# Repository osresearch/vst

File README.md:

v.st vector board
====

This is the firmware and example code for the opensource harwdare
quad-DAC vector board.  It can be used with MAME to display the
vectors from 1970s and 80s games like Starwars or Asteroids
on vectorscopes and XY monitors like the Vectrex, as well as
with new art projects.

More details at https://trmm.net/V.st and https://trmm.net/MAME

## Building the Board
A full Bill of Materials can be found [here](BOM.md).

## Flashing the Firmware
To flash the firmware, make sure you have [Teensyduino](https://www.pjrc.com/teensy/td_download.html) installed.

Clone this repository and load *teensyv/teensyv.ino* in the Arduino IDE. Next select *Teensy 3.1 / 3.2* from the *Tools -> Board* menu in the Arduino IDE. Hit verify and follow the on screen instructions to flash your Teensy with the firmware.

## Running the Demos
Make sure you have [Processing](https://processing.org/) installed and your Teensy is flashed with the firmware.

Open *processingDemo/processingDemo.pde* in Processing. As soon as you hit run and your v.st board is attached to the computer, the demo starts playing on your screen and should be visible on the device attached to your v.st.

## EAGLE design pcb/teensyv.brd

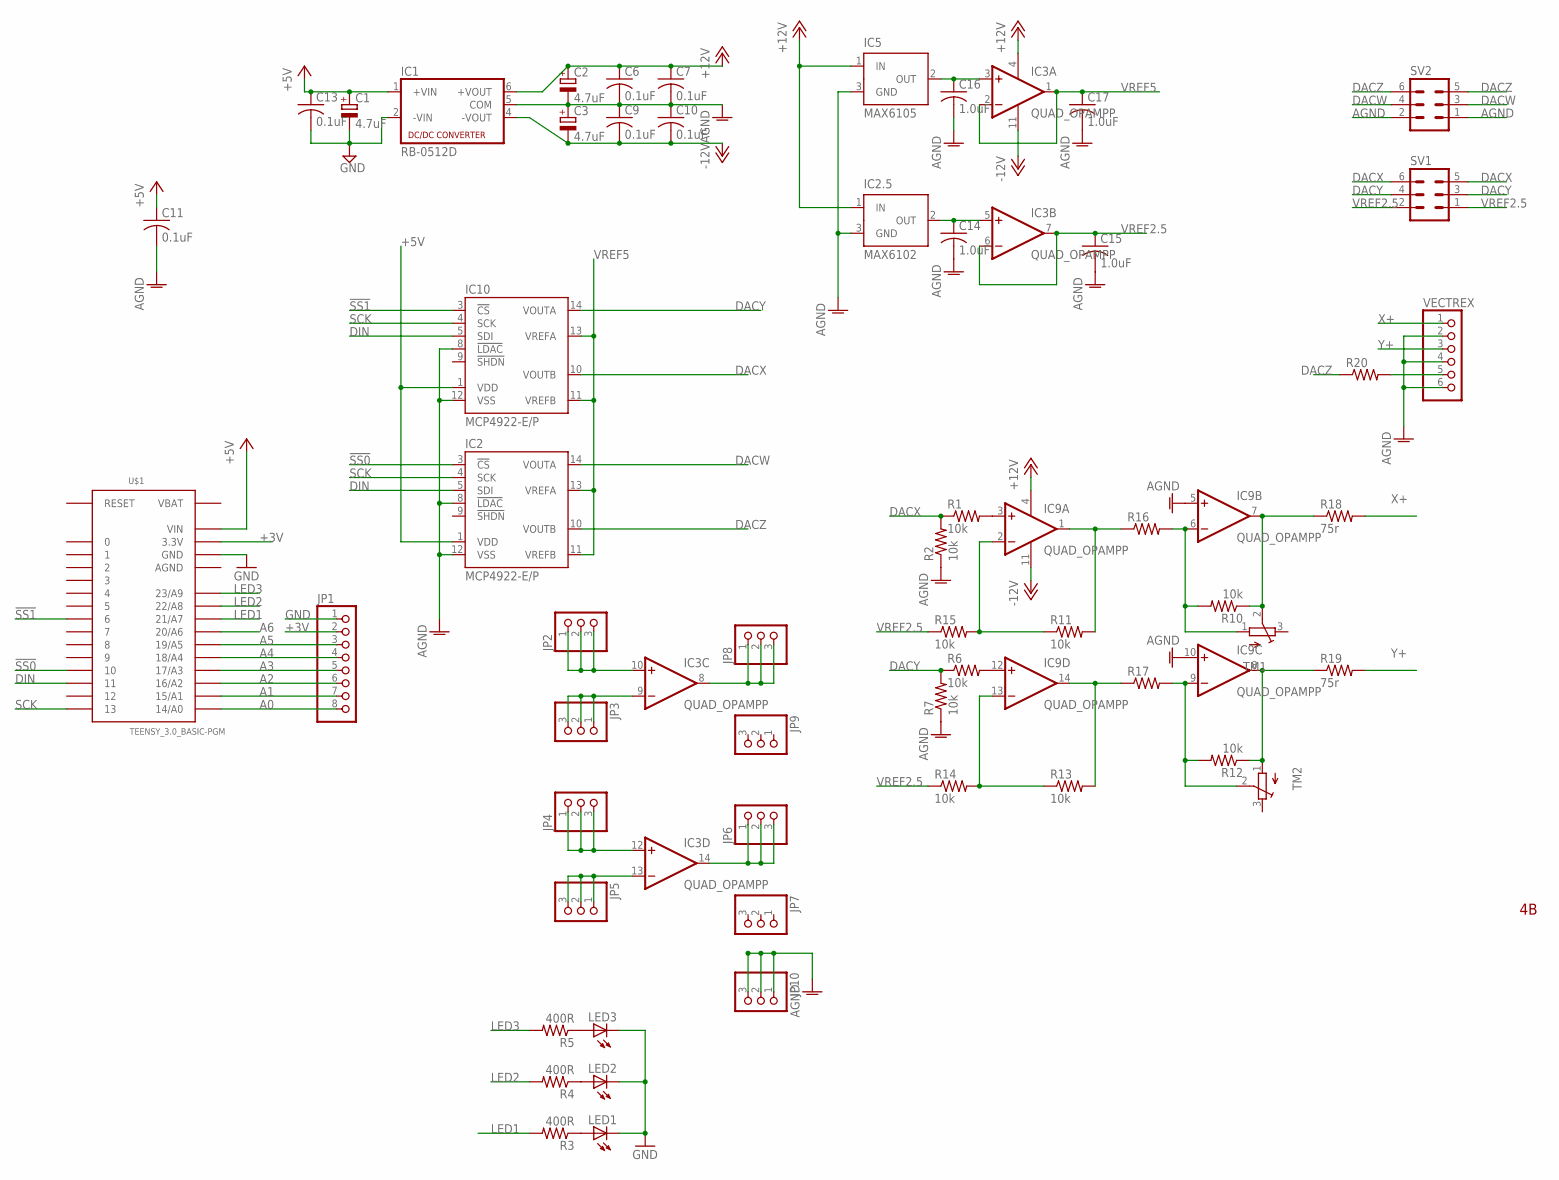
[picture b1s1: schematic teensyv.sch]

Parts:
C1, C2, C3: 4.7uF; E1,8-4
C6, C7, C9, C10, C11, C13: 0.1uF; C025-024X044
C14, C15, C16, C17: 1.0uF; C025-024X044
IC1: RB-0512D; NMA
IC2, IC10: MCP4922-E/P; DIL14
IC2.5: MAX6102; SOT23
IC3, IC9: QUAD_OPAMPP; DIL14
IC5: MAX6105; SOT23
JP1: PINHD-1X8CLEANBIG; 1X08-CLEANBIG
JP2, JP3, JP4, JP5, JP6, JP7, JP8, JP9, JP10: PINHD-1X3; 1X03
LED1, LED2, LED3: LED5MM
R1, R2, R6, R7, R10, R11, R12, R13, R14, R15: 10k; 0204V
R3, R4, R5: 400R; 0204V
R16, R17, R20: R-US_0204/7; 0204/7
R18, R19: 75r; 0204V
SV1, SV2: MA03-2
TM1, TM2: TRIMPOTTC33X; TC33X
U$1: TEENSY_3.0_BASIC-PGM
VECTREX: PINHD-1X6; 1X06

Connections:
!SS0: IC2.3 (!CS), U$1.10
!SS1: IC10.3 (!CS), U$1.6
+3V: JP1.2, U$1.3.3V, U$1.3.3V1 (3.3V)
+5V: C1.+, C11.1, C13.1, IC1.1 (+VIN), IC2.1 (VDD), IC10.1 (VDD), U$1.VIN
+12V: C2.+, C6.1, C7.1, IC1.6 (+VOUT), IC2.5.1 (IN), IC3.4 (V+), IC5.1 (IN), IC9.4 (V+)
-12V: C3.-, C9.2, C10.2, IC1.4 (-VOUT), IC3.11 (V-), IC9.11 (V-)
A0: JP1.8, U$1.14/A0
A1: JP1.7, U$1.15/A1
A2: JP1.6, U$1.16/A2
A3: JP1.5, U$1.17/A3
A4: JP1.4, U$1.18/A4
A5: JP1.3, U$1.19/A5
A6: U$1.20/A6
AGND: C2.-, C3.+, C6.2, C7.2, C9.1, C10.1, C11.2, C14.2, C15.2, C16.2, C17.2, IC1.5 (COM), IC2.8 (!LDAC), IC2.12 (VSS), IC2.5.3 (GND), IC5.3 (GND), IC9.5 (+IN), IC9.10 (+IN), IC10.8 (!LDAC), IC10.12 (VSS), JP10.1, JP10.2, JP10.3, R2.1, R7.1, SV2.1, SV2.2, U$1.AGND, VECTREX.2, VECTREX.4, VECTREX.6
DACW: IC2.14 (VOUTA), SV2.3, SV2.4
DACX: IC10.10 (VOUTB), R1.1, R2.2, SV1.5, SV1.6
DACY: IC10.14 (VOUTA), R6.1, R7.2, SV1.3, SV1.4
DACZ: IC2.10 (VOUTB), R20.1, SV2.5, SV2.6
DIN: IC2.5 (SDI), IC10.5 (SDI), U$1.11
GND: C1.-, C13.2, IC1.2 (-VIN), JP1.1, LED1.K (C), LED2.K (C), LED3.K (C), U$1.GND, U$1.GND1 (GND)
LED1: R3.2, U$1.21/A7
LED2: R4.2, U$1.22/A8
LED3: R5.2, U$1.23/A9
unnamed: C14.1, IC2.5.2 (OUT), IC3.5 (+IN)
unnamed: IC9.3 (+IN), R1.2
unnamed: C16.1, IC3.3 (+IN), IC5.2 (OUT)
unnamed: IC3.13 (-IN), JP5.1, JP5.2, JP5.3
unnamed: IC3.12 (+IN), JP4.1, JP4.2, JP4.3
unnamed: IC3.14 (OUT), JP6.1, JP6.2, JP6.3
unnamed: LED1.A, R3.1
unnamed: IC9.1 (OUT), R11.2, R16.1
unnamed: IC9.12 (+IN), R6.2
unnamed: IC9.2 (-IN), R11.1, R15.2
unnamed: LED2.A, R4.1
unnamed: LED3.A, R5.1
unnamed: IC9.7 (OUT), R10.1, R18.1, TM1.2 (S)
unnamed: IC9.8 (OUT), R12.1, R19.1, TM2.1 (A)
unnamed: IC9.14 (OUT), R13.2, R17.1
unnamed: IC9.9 (-IN), R12.2, R17.2, TM2.2 (S)
unnamed: IC9.6 (-IN), R10.2, R16.2, TM1.1 (A)
unnamed: IC3.9 (-IN), JP3.1, JP3.2, JP3.3
unnamed: IC3.10 (+IN), JP2.1, JP2.2, JP2.3
unnamed: IC3.8 (OUT), JP8.1, JP8.2, JP8.3
unnamed: R20.2, VECTREX.5
SCK: IC2.4 (SCK), IC10.4 (SCK), U$1.13
VBAT: U$1.VBAT
VREF2.5: C15.1, IC3.6 (-IN), IC3.7 (OUT), R14.1, R15.1, SV1.1, SV1.2
VREF5: C17.1, IC2.11 (VREFB), IC2.13 (VREFA), IC3.1 (OUT), IC3.2 (-IN), IC10.11 (VREFB), IC10.13 (VREFA)
X+: R18.2, VECTREX.1
Y+: R19.2, VECTREX.3
YFB: IC9.13 (-IN), R13.1, R14.2

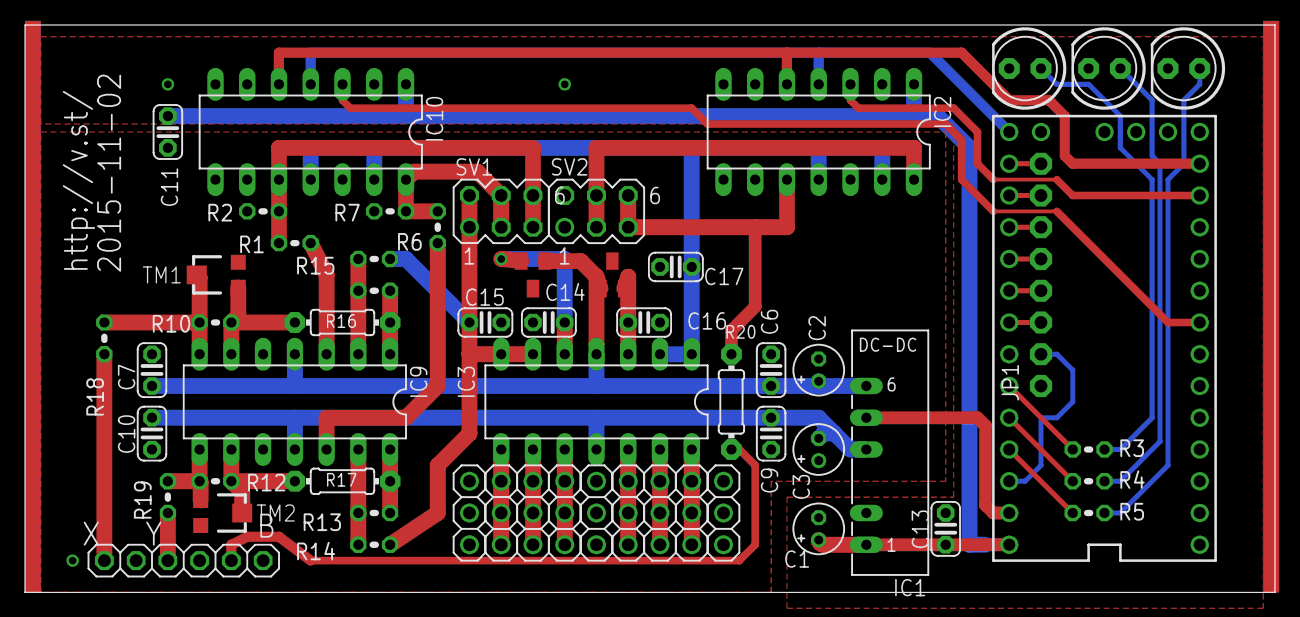
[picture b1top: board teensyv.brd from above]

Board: 2 copper layers, 100.0 x 45.4 mm, 57 parts (0 on the bottom side), 49 nets.

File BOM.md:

# Bill of Materials

| Part             | Purpose/Notes           | Designation                                  | Qty | Supplier Link                                                                                     |
|------------------|-------------------------|----------------------------------------------|-----|---------------------------------------------------------------------------------------------------|
| MAX6105          | 5V reference (FZGX)     | IC5 – right                                  | 1   | https://www.digikey.com/product-detail/en/maxim-integrated/M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 |
| MAX6102          | 2.5V reference (FZGU)   | IC2.5 – left                                 | 1   | https://www.digikey.com/product-detail/en/maxim-integrated/M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 |
| MCP4922 E/P      | 12bit SPI DAC           | IC2, IC10                                    | 2   | https://www.arrow.com/en/products/mcp4922-ep/microchip-technology                                 |
| TL3474 ACN       | 4MHz opamp              | IC3, IC9                                     | 2   | https://www.digikey.com/en/products/detail/texas-instruments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                     |
| RB-0512D         | +/- 12V DC-DC converter | IC1                                          | 1   | https://www.arrow.com/en/products/rb-0512d/recom-power                                            |
| TC33X trimpot    | 20K ohm                 | TM1, TM2                                     | 2   | https://www.arrow.com/en/products/tc33x-2-203e/bourns                                             |
| Teensy 3.2       |                         | TEENSY                                       | 1   | https://www.arrow.com/en/products/dev-13736/sparkfun-electronics                                  |
| 75 ohm resistor  |                         | R18, R19                                     | 2   | https://www.arrow.com/en/products/rnf14ftd75r0/stackpole-ele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                              |
| 10K ohm resistor |                         | R1, R2, R10, R11, R15, R6, R7, R13, R14, R12 | 10  | https://www.arrow.com/en/products/cpf110k000fkb14/vishay                                          |
| 4.7uF cap        |                         | C1, C2, C3                                   | 3   | https://www.arrow.com/en/products/fk28x5r1a475k/tdk                                               |
| 0.1uF cap        |                         | C6, C7, C9, C10, C11, C13                    | 6   | https://www.arrow.com/en/products/k104k15x7rf53l2/vishay                                          |
| 1.0uF cap        |                         | C14, C15, C16, C17                           | 4   | https://www.arrow.com/en/products/sr655c105kartr1/avx                                             |
| 400 ohm resistor |                         | R3, R4, R5                                   | 3   | https://www.digikey.com/en/products/detail/te-connectivity-p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      |
| LED              |                         | LED1, LED2, LED3 (above teensy)              | 3   | https://www.digikey.com/en/products/detail/lite-on-inc/LTL-4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                            |
| 10K ohm resistor |                         | R16, R17, R20                                | 3   | https://www.arrow.com/en/products/cpf110k000fkb14/vishay                                          |
| PCB              |                         |                                              |     | https://oshpark.com/shared_projects/cDeZXhd8                                                      |

**Note:** The precise item numbers for generic parts (resistors, capacitors, LED) were chosen based on availability and price at low quantities in July 2020.

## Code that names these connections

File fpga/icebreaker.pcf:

# 12 MHz clock
set_io -nowarn CLK        35

# RS232
set_io -nowarn serial_rxd          6
set_io -nowarn serial_txd          9

# LEDs and Button
set_io -nowarn BTN_N      10
set_io -nowarn led_r     11
set_io -nowarn led_g     37

# RGB LED Driver
set_io -nowarn R  39
set_io -nowarn G  40
set_io -nowarn B  41

# SPI Flash
set_io -nowarn FLASH_SCK  15
set_io -nowarn FLASH_SSB  16
set_io -nowarn FLASH_IO0  14
set_io -nowarn FLASH_IO1  17
set_io -nowarn FLASH_IO2  12
set_io -nowarn FLASH_IO3  13

# PMOD 1A
set_io -nowarn P1A1        4
set_io -nowarn P1A2        2
set_io -nowarn P1A3       47
set_io -nowarn P1A4       45
set_io -nowarn P1A7        3
set_io -nowarn P1A8       48
set_io -nowarn P1A9       46
set_io -nowarn P1A10      44

# PMOD 1B
set_io -nowarn P1B1       43
set_io -nowarn P1B2       38
set_io -nowarn P1B3       34
set_io -nowarn P1B4       31
set_io -nowarn P1B7       42
set_io -nowarn P1B8       36
set_io -nowarn P1B9       32
set_io -nowarn P1B10      28

# PMOD 2
set_io -nowarn P2_1       27
set_io -nowarn P2_2       25
set_io -nowarn P2_3       21
set_io -nowarn P2_4       19
set_io -nowarn P2_7       26
set_io -nowarn P2_8       23
set_io -nowarn P2_9       20
set_io -nowarn P2_10      18

# LEDs and Buttons (PMOD 2)
set_io -nowarn LED1       27
set_io -nowarn LED2       25
set_io -nowarn LED3       21
set_io -nowarn BTN2       19
set_io -nowarn LED5       26
set_io -nowarn LED4       23
set_io -nowarn BTN1       20
set_io -nowarn BTN3       18

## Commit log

2015-05-09 unipolar stepper x/y works
2015-05-09 rgb laser dimming works (10 is pretty bright)
2015-05-09 phase mapping the full steps
2015-05-09 half stepping with unipolars works
2015-05-09 moved stepper into separate file, made x/y more modular
2015-05-09 moved laser code into separate file
2015-05-09 lineto() function and triangle RGB demo
2015-05-09 readme
2015-05-09 Fixed image link
2015-05-09 circle is rather lopsided
2015-05-15 spi driving the mpc4921 12-bit dacs
2015-05-15 temporarily use the spi4teensy3 library
2015-05-16 mounting brackets for Limor galvos
2015-05-16 precompute sin table for faster drawing
2015-05-16 read input from serial port
2015-07-11 new command protocol
2015-07-11 parameterize brightness
2015-07-16 add debug timing pin output
2015-07-17 work with the dual DAC mpc4922
2015-07-18 hacking on DMA driven SPI (not functional)
2015-07-19 it works, but requires twice as much space in the queue
2015-07-19 DMA SPI works!
2015-07-19 use SS1 for beam on/off and do bresham during beam off cycles
2015-09-24 disable interrupts during wait for dma end
2015-09-25 removed double buffering of input, reduce DMA size and fix partial buffer flush
2015-09-25 mame patch for vector output
2015-09-30 z-axis works, add dwell time during beam transitions, etc
2015-10-03 mame patch to track vector lengths
2015-10-05 increase spi clock to 25 MHz and restore brightness
2015-10-05 move dwell parameters into a function
2015-10-05 increase num points
2015-10-05 asteroids test screen
2015-10-05 updated patch for threshold and debug
2015-10-07 pcb is ready for review
2015-10-07 added LEDs and extra header
2015-10-11 smaller image, startup screen
2015-10-31 flip and swap options, jump option and other things
2015-11-03 reworked board to have two DACs and proper differential amplifier
2015-11-03 ground plane tweaks
2015-11-03 convert to inverting opamp
2015-11-07 slow down DMA clock; clearer output
2015-11-07 parameters that work for the vectorscope
2015-11-21 updates for 2015-11-02 boards, quad dac
2015-11-21 reorganized tree
2015-11-21 reworked most things to be configuration parameters
2015-11-21 better bright parameters
2015-11-21 better bright control for vectorscope
2015-11-21 notes for FLIP parameters
2015-11-21 import and update of Adelles processingToVectrex demo
2015-11-21 random start
2015-11-21 make it qix like
2015-11-21 Image link
2015-11-21 mame patch to reduce build time
2015-11-22 asteroid font drawing works, replaced startup test pattern with better code
2015-11-22 Added scope clock mode with simple font
2015-11-22 start on circle, draw time around the screen
2015-11-23 split scopeclock code into separate file
2015-11-23 analog scope clock works, looks good
2015-11-23 analog scope clock looks great
2015-11-23 second hand and number position tweaks, add option for all 24 hours
2015-11-25 Add support for Hershey simplex font
2015-11-26 UNTESTED mame0168 patch
2015-11-26 update patch and tool to visualize the output
2015-11-27 convert line endings to DOS so that patch does not complain
2015-11-27 make second hand bright
2015-11-27 fix sparkles by ensuring that all DMAs have been sent and tweak vectrex timing paramters for sharpness
2015-11-27 allow lowercase Hershey font and display built time and options on startup screen
2015-11-27 more startup screen tweaks
2015-11-27 split qix code out from driver code
2015-11-27 ignore generated files
2015-11-27 swarm code demo and proper byte buffer handling
2015-11-27 Working patch for mame0168!
2015-11-27 update patch for centering
2015-11-28 add follows mouse mode
2015-11-28 extract vector line drawing out of demo
2015-11-28 started on port of tennis for two
2015-11-28 game seems to work fairly well
2015-11-28 decrease decay slight; very playable
2015-11-28 move offscreen checking into vector.pde
2015-11-29 too much confluence
2015-11-30 tweak brightness values
2015-11-30 start thinking about clipping planes
2015-12-07 test out vector optimization
2015-12-08 Hershey font with example drawing using String.format()
2015-12-08 move font into vector.pde
2015-12-08 split Hershey font back into separate file; added 2D clipping region code
2015-12-08 fix clip check; remove extra lines
2015-12-08 clarify clipping intercept math
2015-12-08 rotating text demo
2015-12-08 add centering if requested
2015-12-10 import of Jakes spiral demo
2015-12-10 tweak recursive parameters slightly
2015-12-10 Note on Jakes demo
2015-12-11 more details
2015-12-11 Improve header docs
2015-12-13 recursive image
2015-12-19 Move clip creation to before serial port initialization to avoid issue #6
2015-12-20 add wrapper for PVector drawing
2015-12-20 3D line art demo using camera projection
2015-12-20 bound and zoom
2015-12-20 ensure path does not intersect and store frames
2015-12-21 unwind the walk after it has been drawn
2015-12-21 throw away bad lines
2015-12-21 fix camera computation and zoom, add outside box
2015-12-21 replace tabs with spaces
2015-12-21 do not draw box, restart random walk where last one finished
2015-12-21 reset clipping every line draw to try to detect resize
2015-12-25 rewrite swarm in terms of PVector 3d math operations
2015-12-29 fix clipping dimensions (issue #7)
2015-12-29 draw box to avoid spot-killer on vectrex
2015-12-29 svg drawing demo (not perfect, but enough for 32c3 logo)
2016-01-08 Created processing folder and moved demo
2016-01-08 Added fireworksDemo
2016-01-08 Removed obsolete files from fireworksDemo
2016-01-08 Removed obsolete code from fireworks demo.
2016-01-08 removed README.md
2016-01-08 Two files were named incorrectly. Fixed.
2016-01-08 Added Firework.pde
2016-01-09 Created VstBuffer class
2016-01-09 Removed IntPoint
2016-01-09 Minor updates
2016-01-09 Make all of the demos use a Demo base class and cycle through them randomly
2016-01-09 udpate copyright and header
2016-01-09 remove Point2 class since it was a duplicate of PVector
2016-01-09 Move clipp code into vector.pde to reduce number of files to have to copy
2016-01-10 Major pass to fireworks demo. Testing VstBuffer as ArrayList<VstFrame>.
2016-01-10 Removed VstBuffer.reset()
2016-01-10 Sorting before buffer send. First pass.
2016-01-10 Cleaned code
2016-01-10 Cleaned code. Consolidated Clipping into VST
2016-01-10 Vst no longer extends Displayable
2016-01-10 Consolidated VstBuffer into VST.pde
2016-01-11 Added section about flashing the firmware and running the Demos.
2016-01-11 Matrix transforms added.
2016-01-11 Vst requires to pass PApplet to constructors. Changed vline, vpoint to line and point.
2016-01-11 Minor changes to class Vst members
2016-01-11 Nearly the simplest example possible.
2016-01-11 Updated fireworks with lastest VST.pde
2016-01-11 Removed obsolete file from basic demo. Updated Vst.pde with import
2016-01-11 Fixed sort. Swapped cmds for first and last segments if continuous lines are drawn in reverse order
2016-01-11 VstBuffer is sorted before displayed to screen.
2016-01-11 Option to display transits
2016-01-12 Synced VST.pde files among demos
2016-01-12 Auto-indent
2016-01-12 Changed the way class Vst handles displaying color by creating members colorNormal, colorBright, colorTransit
2016-01-12 Removed whitespace from basic demo
2016-01-13 Minor. Fixed color
2016-01-13 Minor. Bright lines were being drawn at normal levels
2016-01-13 Synced VST.PDE files in demos
2016-01-13 Fixed bug in fireworks. Normal and Bright levels were swapped.
2016-01-13 pushStyle() and popStyle() pulled outside of display loop in VST.pde.
2016-01-13 Fixed color in fireworks demo
2016-01-13 move dwell function to silence error on 1.6.7 (issue #16)
2016-01-13 Matrix Translations fixed.
2016-01-13 Minor.
2016-01-13 Synced VST.pde files between demos
2016-01-14 move tennis for two into processing directory
2016-01-14 Import the VST.pde file. - Overload `line()` and `ellipse()` - Use the current `stroke()` to set the brightness. - Replace all of the vector line draws demos with `line()`
    Line sorting is slightly broken (issue #18)
2016-01-14 remove ellipse test
2016-01-14 restore other demos
2016-01-14 Fixed sorting to account for different brightness levels for multi-line segments
2016-01-14 BrickBreaker101
2016-01-14 Translating into a Vst game
2016-01-14 Added paddle collision detection and handling
2016-01-14 Ball falls through floor
2016-01-15 Cleanup
2016-01-15 Added walls and changed colors
2016-01-16 Fixed modelX() in VST.line
2016-01-16 fix spelling of vectorscope
2016-01-17 Added 3D method Vst.line(boolean bright, float x0, float y0, float z0, float x1, float y1, float z1)
2016-01-17 Refactored Vst.displayBuffer()
2016-01-17 minor. whitespace
2016-01-17 More refactoring
2016-01-17 started on a vectrex mame cabinet
2016-01-17 tweaked sizes of monitor mounts
2016-01-17 Renamed VstFrame to VstPoint and refactoring it into new places.
2016-01-17 Minor refactor
2016-01-17 float the joystick plate, adjust spacing
2016-01-17 Removed VstBuffer.add(int x, int y, int z). Only VstBuffer.add(VstPoint point) needed now.
2016-01-17 add line() and ellipse() definitions to VST.pde, also add instructions for tabs->spaces for vi users to README
2016-01-18 as cut, mostly. not great
2016-01-18 Major Update! beginShape() vertex() endShape() ellipse()
2016-01-18 Added support for ellipseMode() and brightness level for shapes.
2016-01-18 Overload line(), ellipse(), rect()
2016-01-18 Added more functions, and overloaded a few more
2016-01-18 Fixed parameter names for line() in VstOverload.pde
2016-01-18 Updated all the things
2016-01-18 Removed overloadTest example
2016-01-18 Updated fireworkDemo using new VST.pde
2016-01-18 Updated BrickBreaking101 to use new VST.pde
2016-01-18 simple joystick interface for the teensy 2
2016-01-19 Fixed 3D? Using screenXYZ() instead of modelXYZ().
2016-01-19 Added spiral3D demo. Needed a sketch to test 3D transformations.
2016-01-19 Updated look of spiral3D
2016-01-19 spiral3D use VstOverload
2016-01-19 In 3D, lines are clipped at the z-plane. Does not support camera() features of Processing
2016-01-21 Updated processingDemo. Orgranized with Demo engine and demos now draw from VstBuffer
2016-01-21 Fixed issues from conversion to new Demo engine
2016-01-21 Using pushStyle() matrix for strokes in demos.
2016-01-21 Changes to svg demo, but currently disabled
2016-01-21 Ensure new randomly selected demo is not the same as the last
2016-01-21 FramesLeft were off by one.
2016-01-30 Converting to 4-bytes, first pass
2016-01-30 Fixed color
2016-01-30 Use a 4-byte protocol with explicit brightness on each line segment (Issue #1)
2016-01-30 fix centering on screen
2016-01-30 replace VST.pde files with symlink and update code to work with new new API
2016-01-31 Starting process of resolving conflicts between versions
2016-01-31 Changes to VstBuffer
2016-01-31 Updated most demos
2016-01-31 Added to VstOverload
2016-01-31 Combined overloaded methods with VST
2016-01-31 Added triangle and quad to overloaded vst functions
2016-01-31 Synced examples
2016-01-31 Possibly fixed transit for every draw
2016-02-06 vst.strokeColor defaults to 255
2016-02-06 First point is entered to center vector turtle at beginning of new grame.
2017-03-19 LBO-51MA configuration
2019-04-21 ignore FPGA files
2019-04-21 import of FPGA DAC from up5k tree
2019-04-21 split mpc into separate file
2019-04-21 fix verilog test generation
2019-04-21 lineto algorithm
2019-04-21 use the lineto to draw on the mpc
2021-05-16 Added bill of materials
    BOM based on what I ordered to build it (minus sockets and such)
2021-05-16 Added newline in README.md
2021-05-18 Added support for vacuum tube oscilloscope
    I have an Analab Type 1100 from the year 1960, which uses vacuum
    tubes instead of transistors and is thus slower to respond than
    more modern tubes.
    Define CONFIG_TUBE to slow down the beam for this scope.
